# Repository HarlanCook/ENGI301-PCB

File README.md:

# ENGI301-PCB

Etch-A-Sketch Printed Circuit Board
Harlan Cook
ENGI 301
Welsh

Files for the production of a PCB that will be combined with the PocketBeagle and several other components to make a simple digital etch-a-sketch.

EAGLE contains Eagle files such as the library (.lbr), board (.brd), and schematics (.sch) that can be opened in Eagle or other PCB CAM editors. They contain the appropriate documentation for understanding the electronics and components used. This folder also contains the gerber files necessary to produce the board.
MFG contains mechanical diagrams of the top and bottom of the board, as well as a simplfiied mechanical block diagram.

Other files are .pdf 's of the board and electrical schematics, also a Bill of Materials (BOM) .csv

Special notes:
This project is made to work specifically with a PocketBeagle (https://beagleboard.org/pocket) and an Adafruit SPI screen (https://www.adafruit.com/product/1770)

Acknowledgements to the manufacturers of the PocketBeagle and Adafruit screen for their CAD references, as well as to Erik Welsh who created many of the library files and gave detailed instructions for this project's completion.

Copyright (c) [2022] [Harlan Cook]

Permission is hereby granted, free of charge, to any person obtaining a copy
of this software and associated documentation files (the "Software"), to deal
in the Software without restriction, including without limitation the rights
to use, copy, modify, merge, publish, distribute, sublicense, and/or sell
copies of the Software, and to permit persons to whom the Software is
furnished to do so, subject to the following conditions:

The above copyright notice and this permission notice shall be included in all
copies or substantial portions of the Software.

THE SOFTWARE IS PROVIDED "AS IS", WITHOUT WARRANTY OF ANY KIND, EXPRESS OR
IMPLIED, INCLUDING BUT NOT LIMITED TO THE WARRANTIES OF MERCHANTABILITY,
FITNESS FOR A PARTICULAR PURPOSE AND NONINFRINGEMENT. IN NO EVENT SHALL THE
AUTHORS OR COPYRIGHT HOLDERS BE LIABLE FOR ANY CLAIM, DAMAGES OR OTHER
LIABILITY, WHETHER IN AN ACTION OF CONTRACT, TORT OR OTHERWISE, ARISING FROM,
OUT OF OR IN CONNECTION WITH THE SOFTWARE OR THE USE OR OTHER DEALINGS IN THE
SOFTWARE.

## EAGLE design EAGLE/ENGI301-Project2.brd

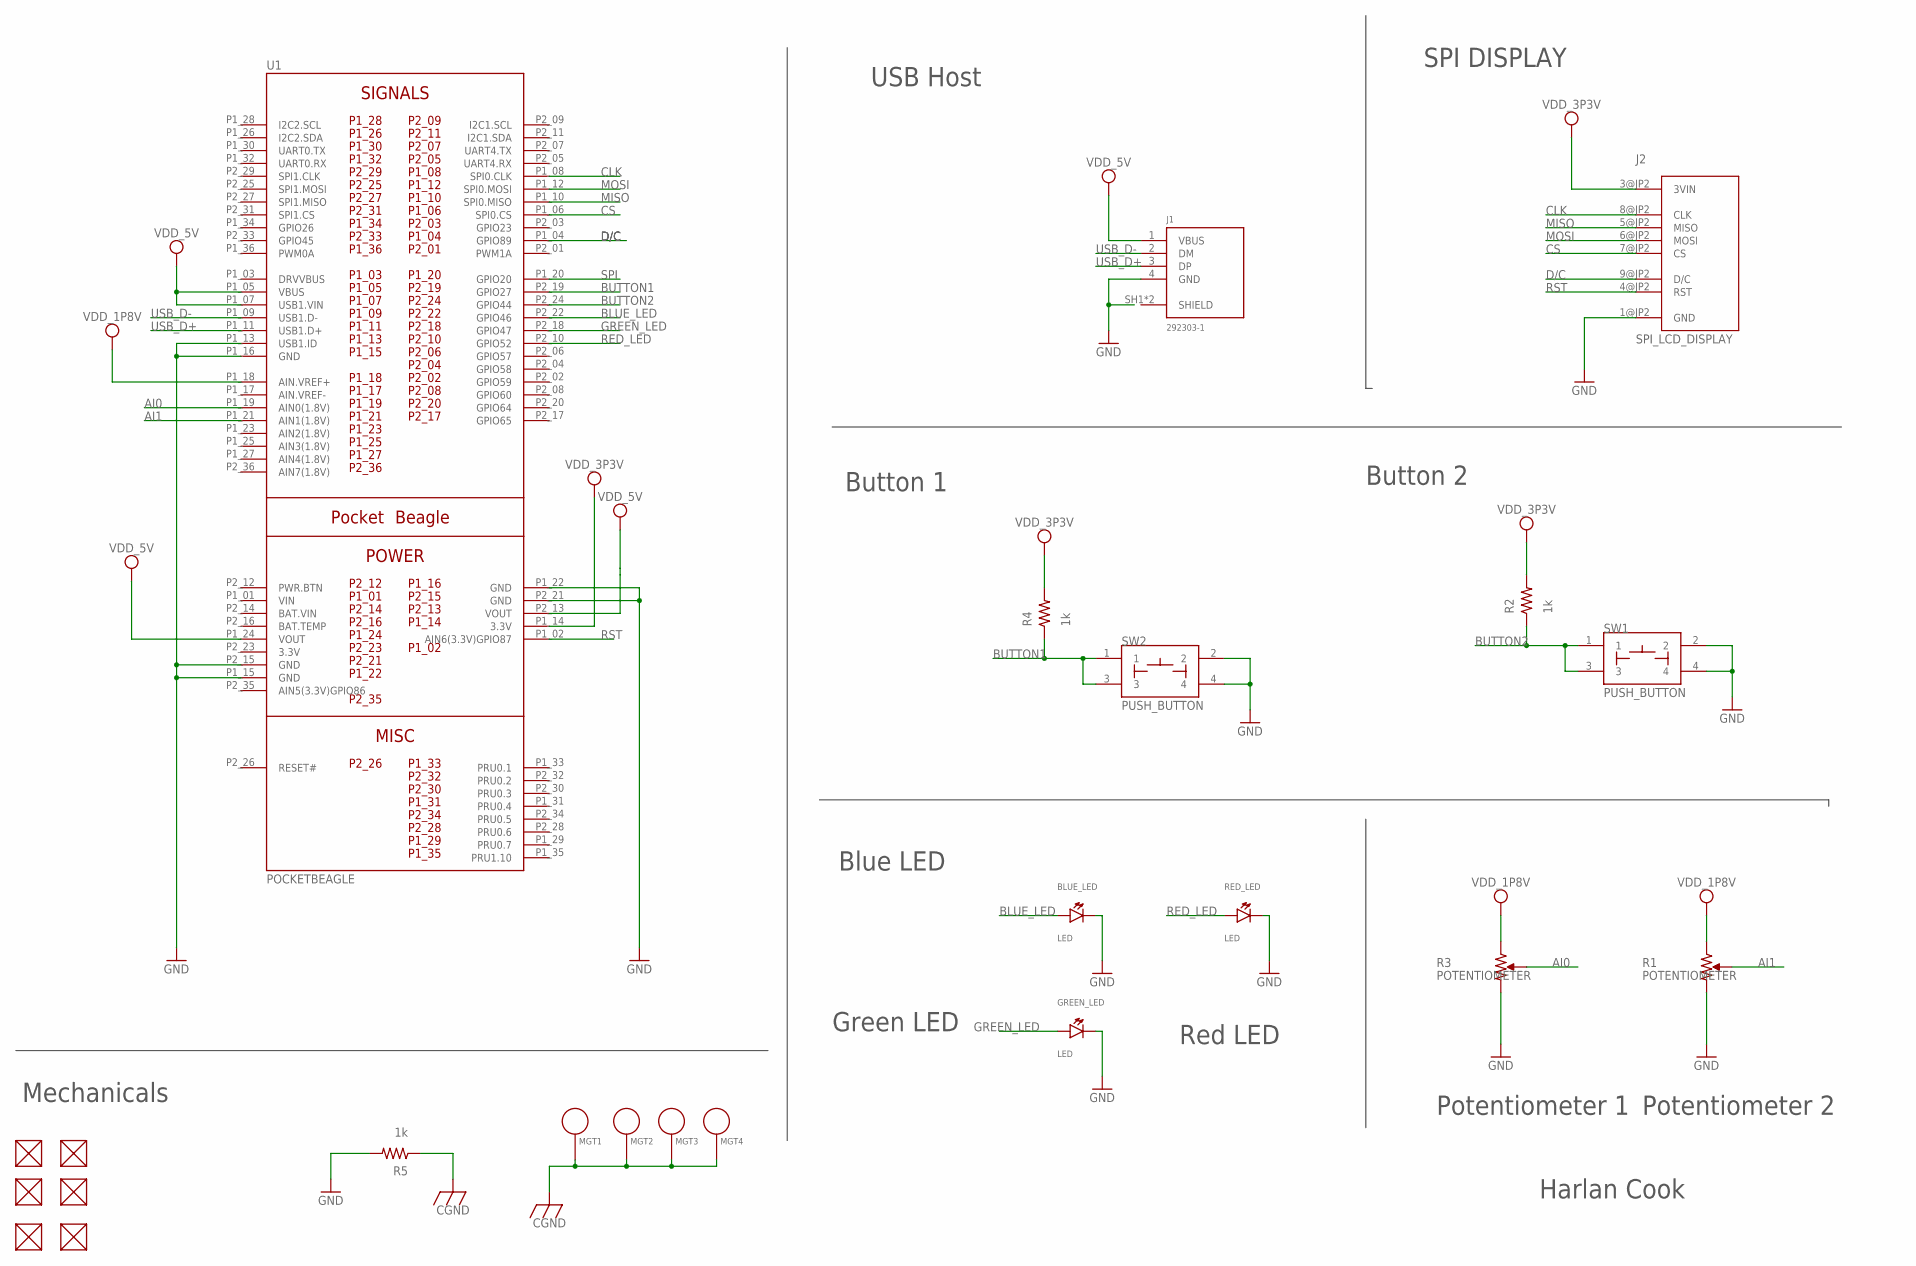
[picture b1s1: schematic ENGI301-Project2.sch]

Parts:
BLUE_LED: LED; EIA-STD
FUD1, FUD2, FUD3, FUD4, FUD5, FUD6: FIDUCIAL; FIDUCIAL_40MIL
GREEN_LED: LED; EIA-STD
J1: 292303-1; TE_292303-1
J2: SPI_LCD_DISPLAY
MGT1, MGT2, MGT3, MGT4: MOUNTING_HOLE
R1, R3: POTENTIOMETER; POT-PO90S
R2, R4, R5: 1k; R0402
RED_LED: LED; EIA-STD
SW1, SW2: PUSH_BUTTON; BUTTON_12.5MM
U1: POCKETBEAGLE

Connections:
3.3V: U1.P2_23 (3.3V)
AI0: R3.S, U1.P1_19 (AIN0(1.8V))
AI1: R1.S, U1.P1_21 (AIN1(1.8V))
BAT.VIN: U1.P2_14 (BAT.VIN)
BLUE_LED: BLUE_LED.ANODE, U1.P2_22 (GPIO46)
BUTTON1: R4.1, SW2.1, SW2.3, U1.P2_19 (GPIO27)
BUTTON2: R2.1, SW1.1, SW1.3, U1.P2_24 (GPIO44)
CGND: MGT1.P$1, MGT2.P$1, MGT3.P$1, MGT4.P$1, R5.1
CLK: J2.8@JP2 (CLK), U1.P1_08 (SPI0.CLK)
CS: J2.7@JP2 (CS), U1.P1_06 (SPI0.CS)
D/C: J2.9@JP2 (D/C), U1.P1_04 (GPIO89)
GND: BLUE_LED.CATHODE, GREEN_LED.CATHODE, J1.4 (GND), J2.1@JP2 (GND), R1.CW, R3.CW, R5.2, RED_LED.CATHODE, SW1.2, SW1.4, SW2.2, SW2.4, U1.P1_13 (USB1.ID), U1.P1_15 (GND), U1.P1_16 (GND), U1.P1_22 (GND), U1.P2_15 (GND), U1.P2_21 (GND)
GREEN_LED: GREEN_LED.ANODE, U1.P2_18 (GPIO47)
MISO: J2.5@JP2 (MISO), U1.P1_10 (SPI0.MISO)
MOSI: J2.6@JP2 (MOSI), U1.P1_12 (SPI0.MOSI)
RED_LED: RED_LED.ANODE, U1.P2_10 (GPIO52)
RST: J2.4@JP2 (RST), U1.P1_02 (AIN6(3.3V)GPIO87)
SPI: U1.P1_20 (GPIO20)
USB_D+: J1.3 (DP), U1.P1_11 (USB1.D+)
USB_D-: J1.2 (DM), U1.P1_09 (USB1.D-)
VDD_1P8V: R1.CCW, R3.CCW, U1.P1_18 (AIN.VREF+)
VDD_3P3V: J2.3@JP2 (3VIN), R2.2, R4.2, U1.P1_14 (3.3V)
VDD_5V: J1.1 (VBUS), U1.P1_05 (VBUS), U1.P1_07 (USB1.VIN), U1.P1_24 (VOUT), U1.P2_13 (VOUT)
VIN: U1.P1_01 (VIN)

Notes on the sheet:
USB Host
SPI DISPLAY
Button 1
Button 2
Blue LED
Green LED
Red LED
Potentiometer 1
Potentiometer 2
Mechanicals
Harlan Cook

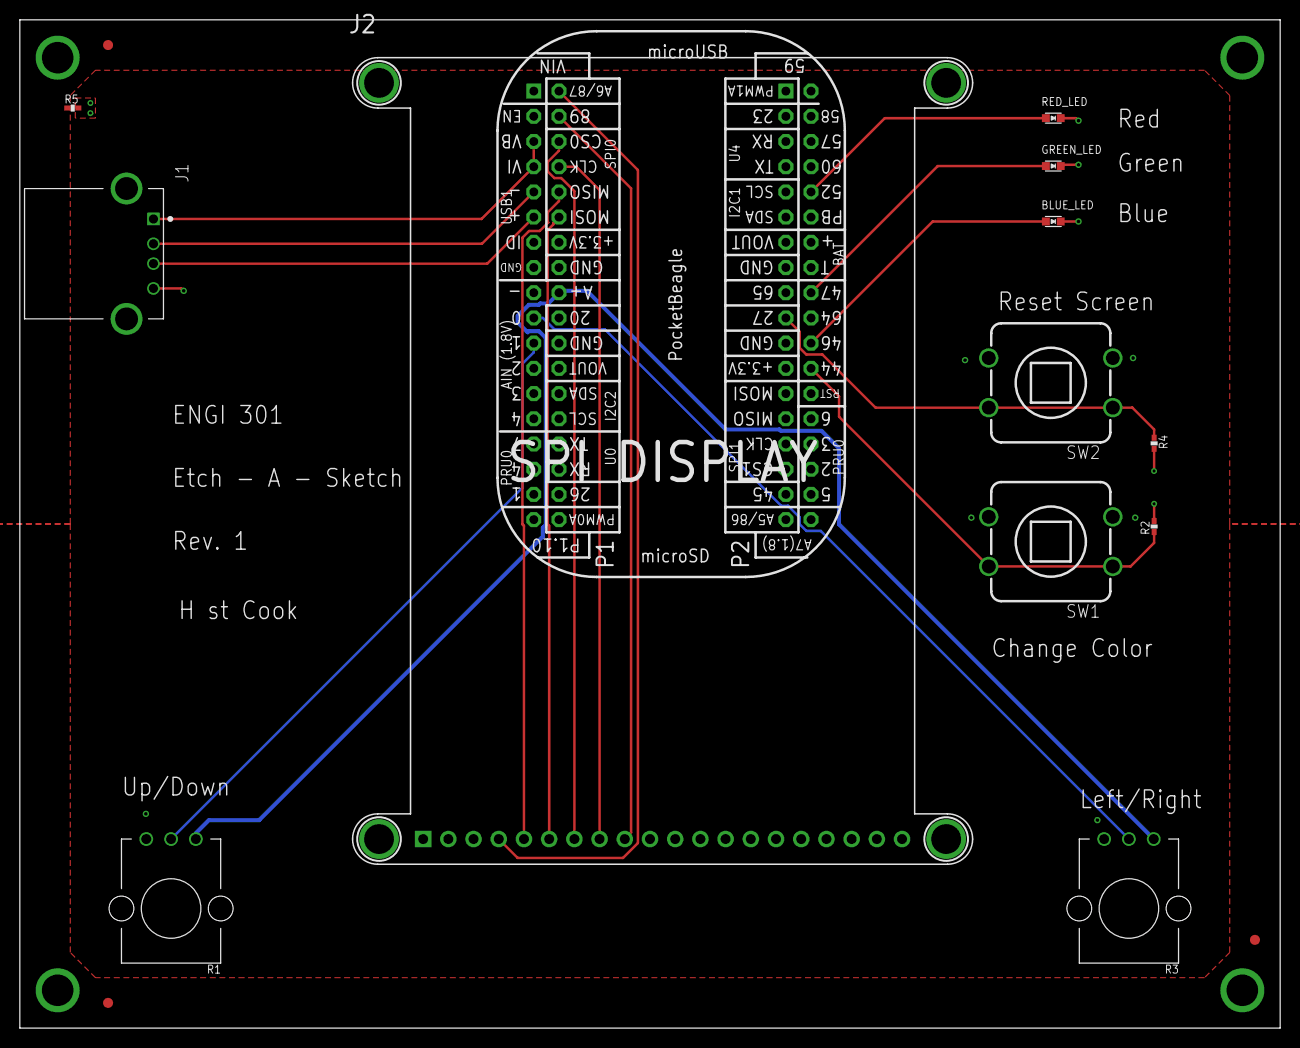
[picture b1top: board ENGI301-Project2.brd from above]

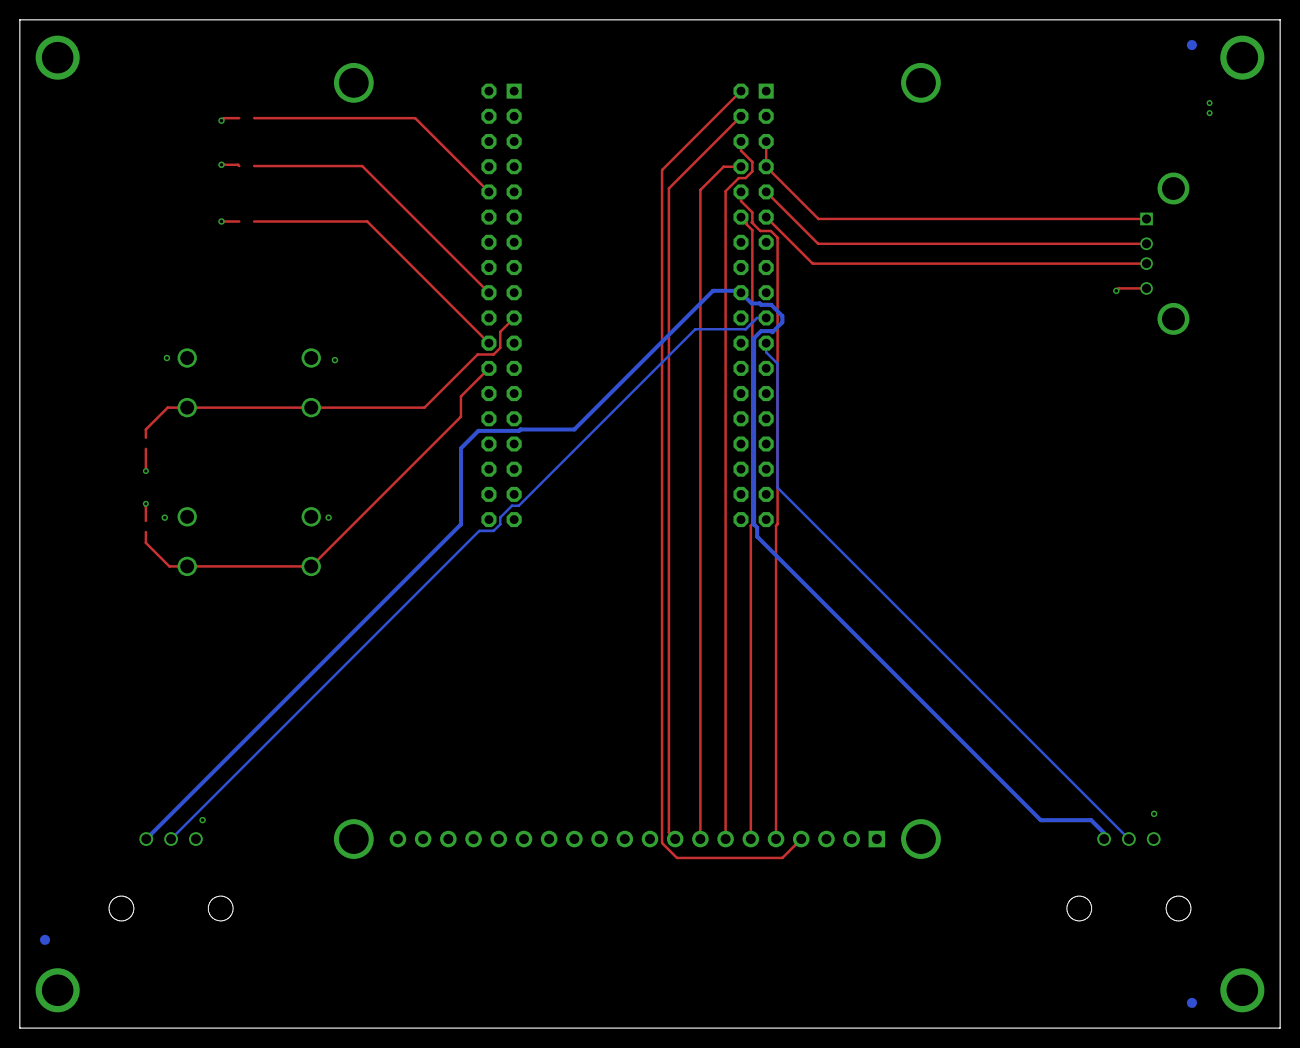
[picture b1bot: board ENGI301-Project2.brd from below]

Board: 4 copper layers, 127.0 x 101.6 mm, 23 parts (3 on the bottom side), 20 nets.

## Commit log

2022-12-14 Create EAGLE
2022-12-14 Update EAGLE
2022-12-14 EAGLE
    Eagle sub-folder containing .lbr, .brd, and .sch files for the project
2022-12-14 MFG
    Manufacturing sub-folder containing top and bottom schematics of how to board will physically look and gerber files
2022-12-14 Update README.md
    readme update
2022-12-14 Eagle folder making
2022-12-14 Add files via upload
    Eagle library, schematics, and board files for the etch a sketch project
2022-12-14 Create Top
2022-12-14 Add files via upload
    Mechanical drawings of the top and bottom of the etch a sketch board
2022-12-14 Create g
2022-12-14 Bill of Materials (BOM)
